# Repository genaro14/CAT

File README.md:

# CAT
Controlador abierto de temperatura y RGB

Ejemplo básico encendido Fading Led 
for int i=0; i < 255; i++{
analogWrite(ledPin,i);
delayMicroseconds(delayN);
}

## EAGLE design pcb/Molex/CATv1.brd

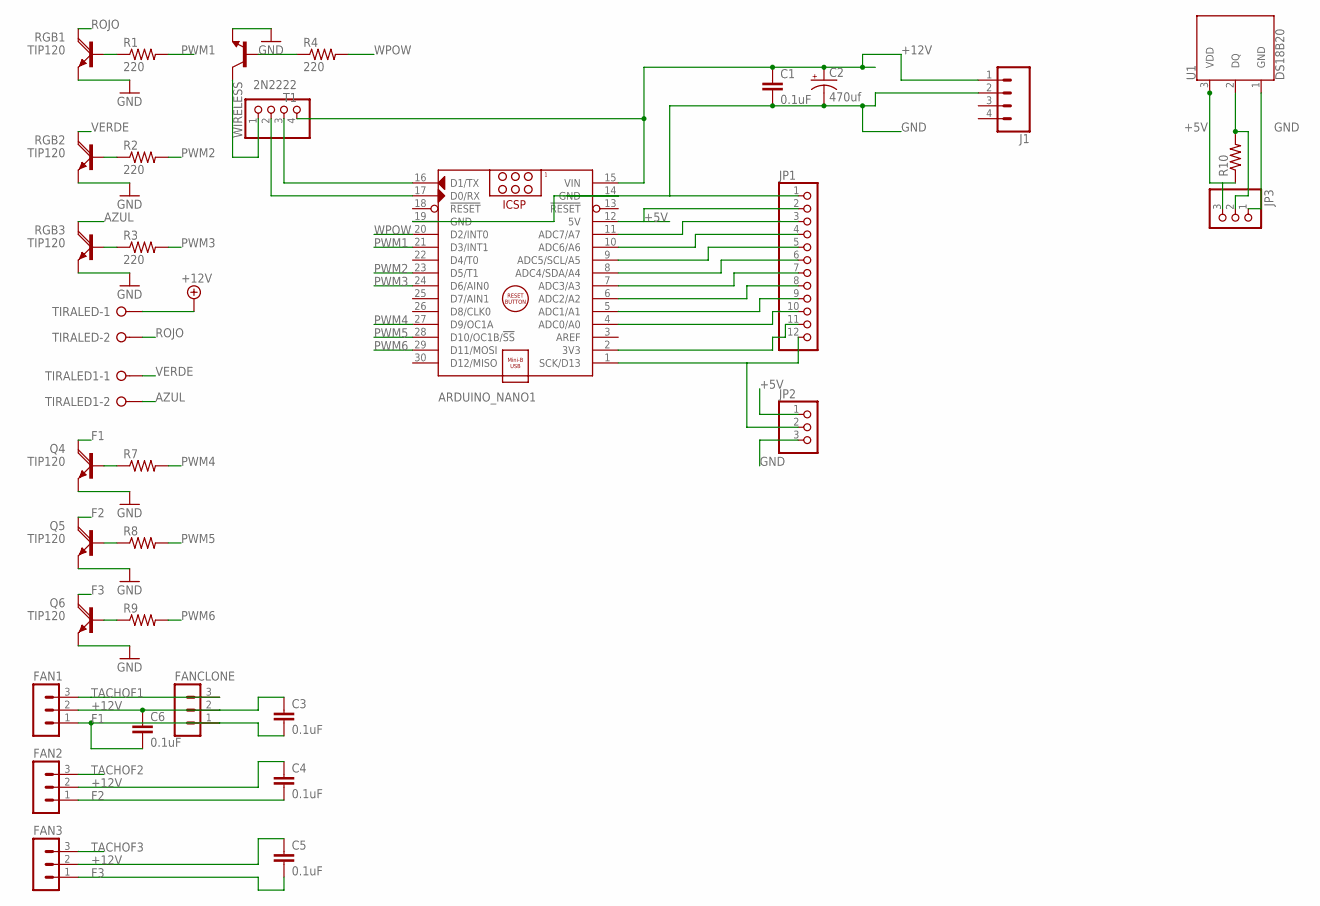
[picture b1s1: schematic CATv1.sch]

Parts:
ARDUINO_NANO1: ARDUINO_NANO
C1, C3, C4, C5, C6: 0.1uF; CAP-PTH-SMALL-KIT
C2: 470uf; E5-10,5
FAN1, FAN2, FAN3: MA03-1
FANCLONE: MA03-1
J1: CONN_04POLAR; MOLEX-1X4
JP1: PINHD-1X12; 1X12
JP2, JP3: PINHD-1X3; 1X03
Q4, Q5, Q6: TIP120; TO220AH
R1, R2, R3: 220; 0207/10
R4: 220; 0207/12
R7, R8, R9, R10: R-US_0207/10; 0207/10
RGB1, RGB2, RGB3: TIP120; TO220AH
T1: 2N2222; TO92-EBC-OVAL
TIRALED, TIRALED1: W237-02P; W237-132
U1: DS18B20; TO-92-AMMO
WIRELESS: PINHD-1X4; 1X04

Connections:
+5V: ARDUINO_NANO1.12 (5V), JP1.2, JP2.1, JP3.3, R10.1, U1.3 (VDD)
+12V: ARDUINO_NANO1.15 (VIN), C1.1, C2.+, C3.1, C4.1, C5.1, C6.1, FAN1.2, FAN2.2, FAN3.2, FANCLONE.2, J1.1, TIRALED.1, WIRELESS.4
AZUL: RGB3.C, TIRALED1.2
F1: C3.2, C6.2, FAN1.1, FANCLONE.1, Q4.C
F2: C4.2, FAN2.1, Q5.C
F3: C5.2, FAN3.1, Q6.C
GND: ARDUINO_NANO1.14 (GND), ARDUINO_NANO1.19 (GND), C1.2, C2.-, J1.2, JP1.1, JP2.3, JP3.1, Q4.E, Q5.E, Q6.E, RGB1.E, RGB2.E, RGB3.E, T1.E, U1.1 (GND)
unnamed: ARDUINO_NANO1.16 (D1/TX), WIRELESS.3
unnamed: ARDUINO_NANO1.17 (D0/RX), WIRELESS.2
unnamed: R1.1, RGB1.B
unnamed: R2.1, RGB2.B
unnamed: R3.1, RGB3.B
unnamed: JP3.2, R10.2, U1.2 (DQ)
unnamed: ARDUINO_NANO1.2 (3V3), JP1.11
unnamed: ARDUINO_NANO1.11 (ADC7/A7), JP1.3
unnamed: ARDUINO_NANO1.10 (ADC6/A6), JP1.4
unnamed: ARDUINO_NANO1.9 (ADC5/SCL/A5), JP1.5
unnamed: ARDUINO_NANO1.1 (SCK/D13), JP1.12, JP2.2
unnamed: ARDUINO_NANO1.8 (ADC4/SDA/A4), JP1.6
unnamed: ARDUINO_NANO1.7 (ADC3/A3), JP1.7
unnamed: ARDUINO_NANO1.6 (ADC2/A2), JP1.8
unnamed: Q4.B, R7.1
unnamed: Q5.B, R8.1
unnamed: Q6.B, R9.1
unnamed: ARDUINO_NANO1.5 (ADC1/A1), JP1.9
unnamed: ARDUINO_NANO1.4 (ADC0/A0), JP1.10
unnamed: R4.1, T1.B
unnamed: T1.C, WIRELESS.1
PWM1: ARDUINO_NANO1.21 (D3/INT1), R1.2
PWM2: ARDUINO_NANO1.23 (D5/T1), R2.2
PWM3: ARDUINO_NANO1.24 (D6/AIN0), R3.2
PWM4: ARDUINO_NANO1.27 (D9/OC1A), R7.2
PWM5: ARDUINO_NANO1.28 (D10/OC1B/!SS), R8.2
PWM6: ARDUINO_NANO1.29 (D11/MOSI), R9.2
ROJO: RGB1.C, TIRALED.2
TACHOF1: FAN1.3, FANCLONE.3
TACHOF2: FAN2.3
TACHOF3: FAN3.3
VERDE: RGB2.C, TIRALED1.1
WPOW: ARDUINO_NANO1.20 (D2/INT0), R4.2

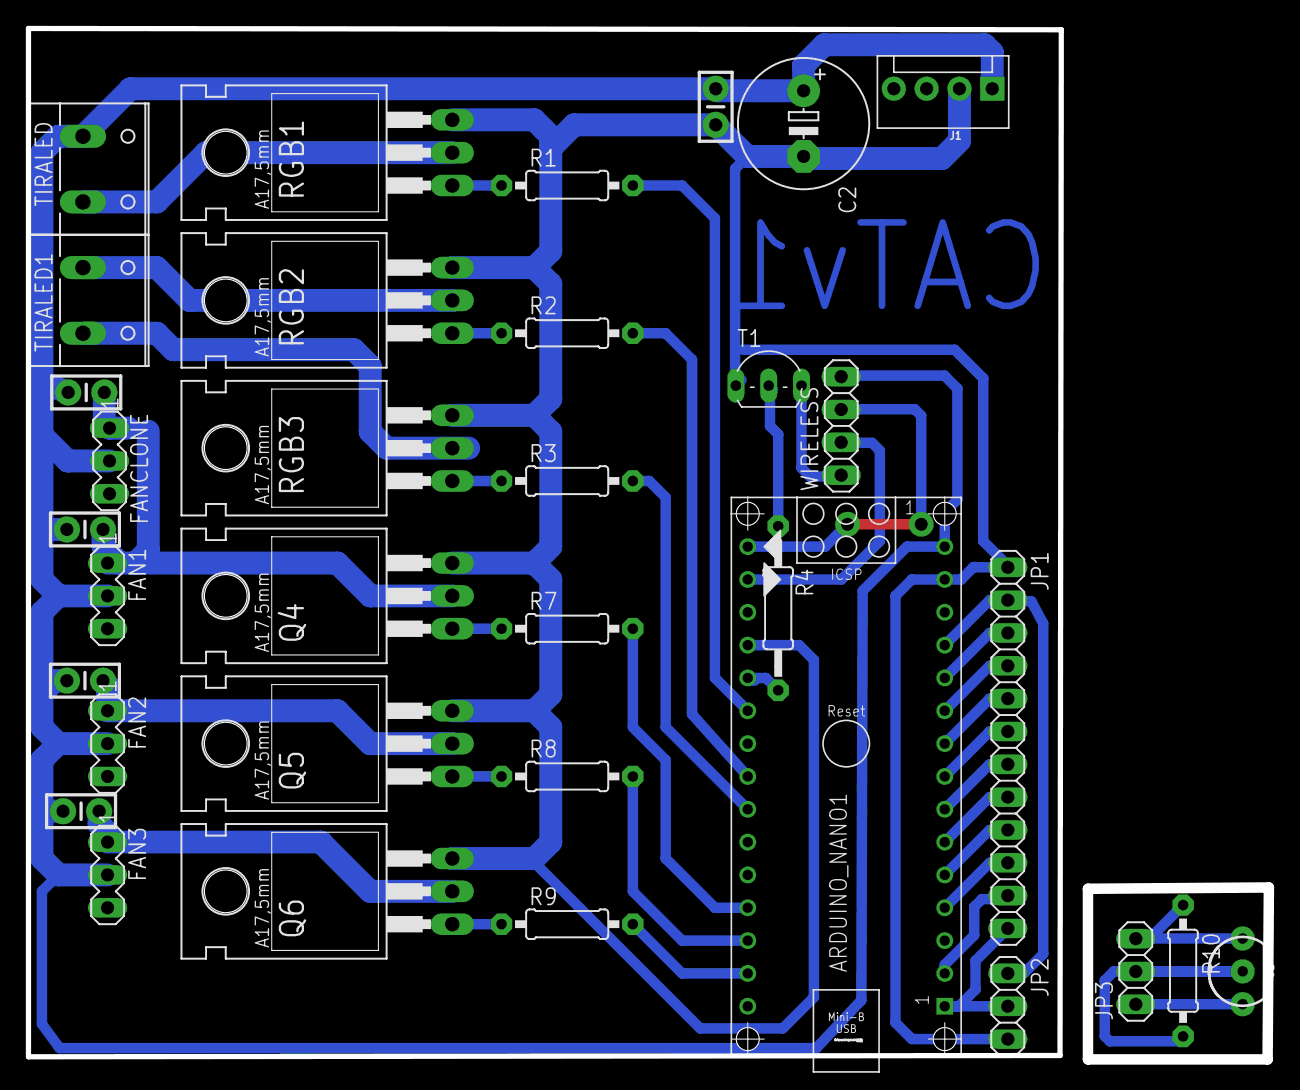
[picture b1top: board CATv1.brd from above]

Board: 2 copper layers, 95.8 x 79.6 mm, 34 parts (0 on the bottom side), 38 nets.

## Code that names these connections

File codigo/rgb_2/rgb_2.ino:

/* www.educachip.com */

//Se definen las variables que se van a utilizar para establecer los
//colores. Éstas deben estar asociadas a pines digitales PWM e irán
//unidas a los cátodos de cada uno de los colores.
int Rojo = 3;
int Verde = 11;
int Azul = 10;

//Se almacenan los valores relativos a la intensidad de cada color
//(las candelas de cada color).
int mcdRojo = 300;
int mcdVerde = 1000;
int mcdAzul = 400;

//Se realiza una relación entre las candelas de los distintos
//colores.
int GradoRojo = (mcdRojo / mcdVerde);
int GradoVerde = (mcdVerde / mcdVerde);
int GradoAzul = (mcdAzul / mcdVerde);

void setup() {

  //Se establecen los pines definidos como salidas para poder
  //la diferencia de voltaje con respecto a la alimentación común.
  pinMode(Rojo, OUTPUT);
  pinMode(Verde, OUTPUT);
  pinMode(Azul, OUTPUT);

}

//Se crea un módulo auxiliar que facilitará la tarea de establecer
//los voltajes asociados a cada color.
//El valor de las variables R, G y B debe ser un entero entre 0 y 255
//siendo 255 el valor relativo a la máxima luminosidad de cada color.
void EstablecerColor(int R, int G, int B) {

  //Se utiliza la expresión X/GradoX para multiplicar el valor de la
  //salida PWM por un número que consiga una intensidad de luz
  //equiparable entre todos los colores.
  //Se debe tener en cuenta que la salida máxima es 255, por tanto,
  //la compensación entre los colores se pierde si la relación
  //X/GradoX genera un valor superior a 255.
  analogWrite(Rojo, (R / GradoRojo));
  analogWrite(Verde, (G / GradoVerde));
  analogWrite(Azul, (B / GradoAzul));

}

void loop() {

  //Se representan colores pseudoaleatorios en el LED RGB mediante el
  //uso de la instrución random(min,max);.
  EstablecerColor(random(0, 255), random(0, 255), random(0, 255));

  //Se utiliza un delay para que de tiempo algo observador a apreciar
  //los colores.
  delay(1000);

}

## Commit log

2017-10-03 CAT Repo upload
2017-10-14 Nueva version borneras y rastnest
2018-06-13 Update README.md
    Readme update

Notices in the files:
parts and their libraries:
SparkFun-Sensors: Licensing: Creative Commons ShareAlike 4.0 International - https://creativecommons.org/licenses/by-sa/4.0
